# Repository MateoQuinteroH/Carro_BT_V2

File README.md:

# Carro_BT_V2
Carro basado en arduino Nano controlado mediante una aplicación Android

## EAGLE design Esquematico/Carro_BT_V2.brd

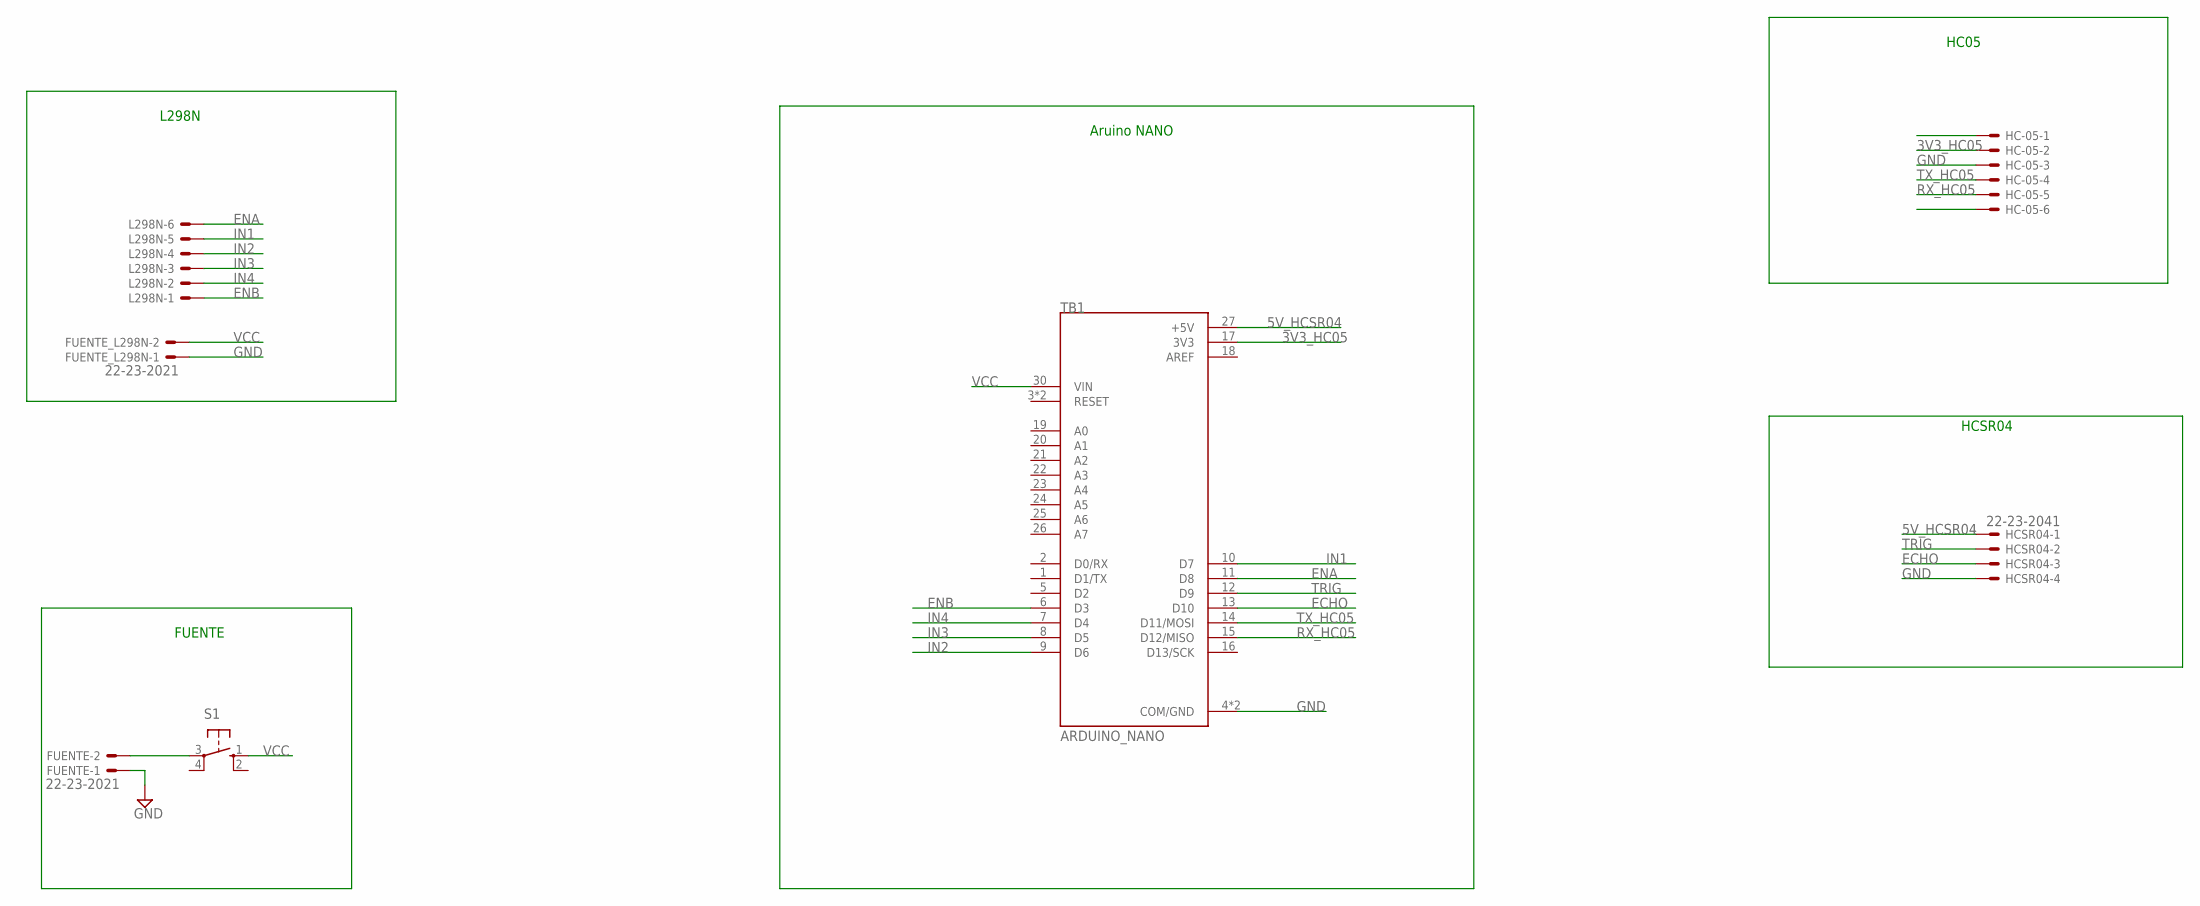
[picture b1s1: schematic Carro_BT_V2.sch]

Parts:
FUENTE: 22-23-2021
FUENTE_L298N: 22-23-2021
HC-05: 22-23-2061
HCSR04: 22-23-2041
L298N: 22-23-2061
S1: 10-XX; B3F-10XX
TB1: ARDUINO_NANO; SHIELD_ARDUINO_NANO

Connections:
3V3_HC05: HC-05.2, TB1.17 (3V3)
5V_HCSR04: HCSR04.1, TB1.27 (+5V)
AREF: TB1.18 (AREF)
ECHO: HCSR04.3, TB1.13 (D10)
ENA: L298N.6, TB1.11 (D8)
ENA1: HC-05.6
ENB: L298N.1, TB1.6 (D3)
ENB1: HC-05.1
GND: FUENTE.1, FUENTE_L298N.1, HC-05.3, HCSR04.4, TB1.4 (COM/GND), TB1.29 (COM/GND)
IN1: L298N.5, TB1.10 (D7)
IN2: L298N.4, TB1.9 (D6)
IN3: L298N.3, TB1.8 (D5)
IN4: L298N.2, TB1.7 (D4)
unnamed: FUENTE.2, S1.3
RX_HC05: HC-05.5, TB1.15 (D12/MISO)
TRIG: HCSR04.2, TB1.12 (D9)
TX_HC05: HC-05.4, TB1.14 (D11/MOSI)
VCC: FUENTE_L298N.2, S1.1 (S), TB1.30 (VIN)

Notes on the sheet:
Aruino NANO
L298N
HC05
HCSR04
FUENTE

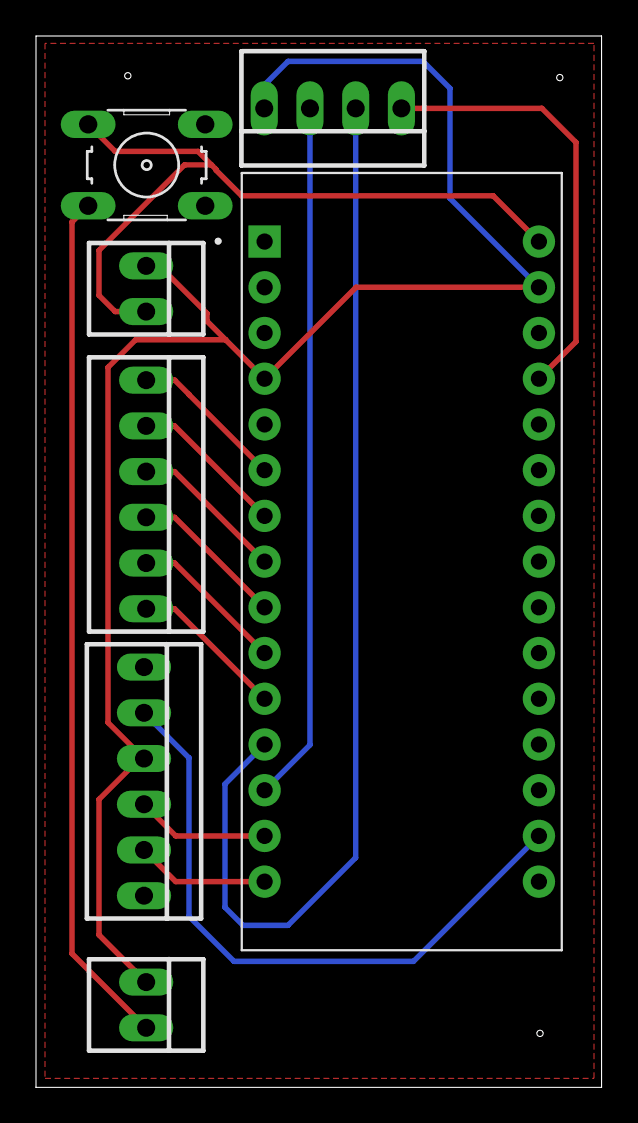
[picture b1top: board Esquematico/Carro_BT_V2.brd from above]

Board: 2 copper layers, 31.4 x 58.4 mm, 7 parts (0 on the bottom side), 15 nets.

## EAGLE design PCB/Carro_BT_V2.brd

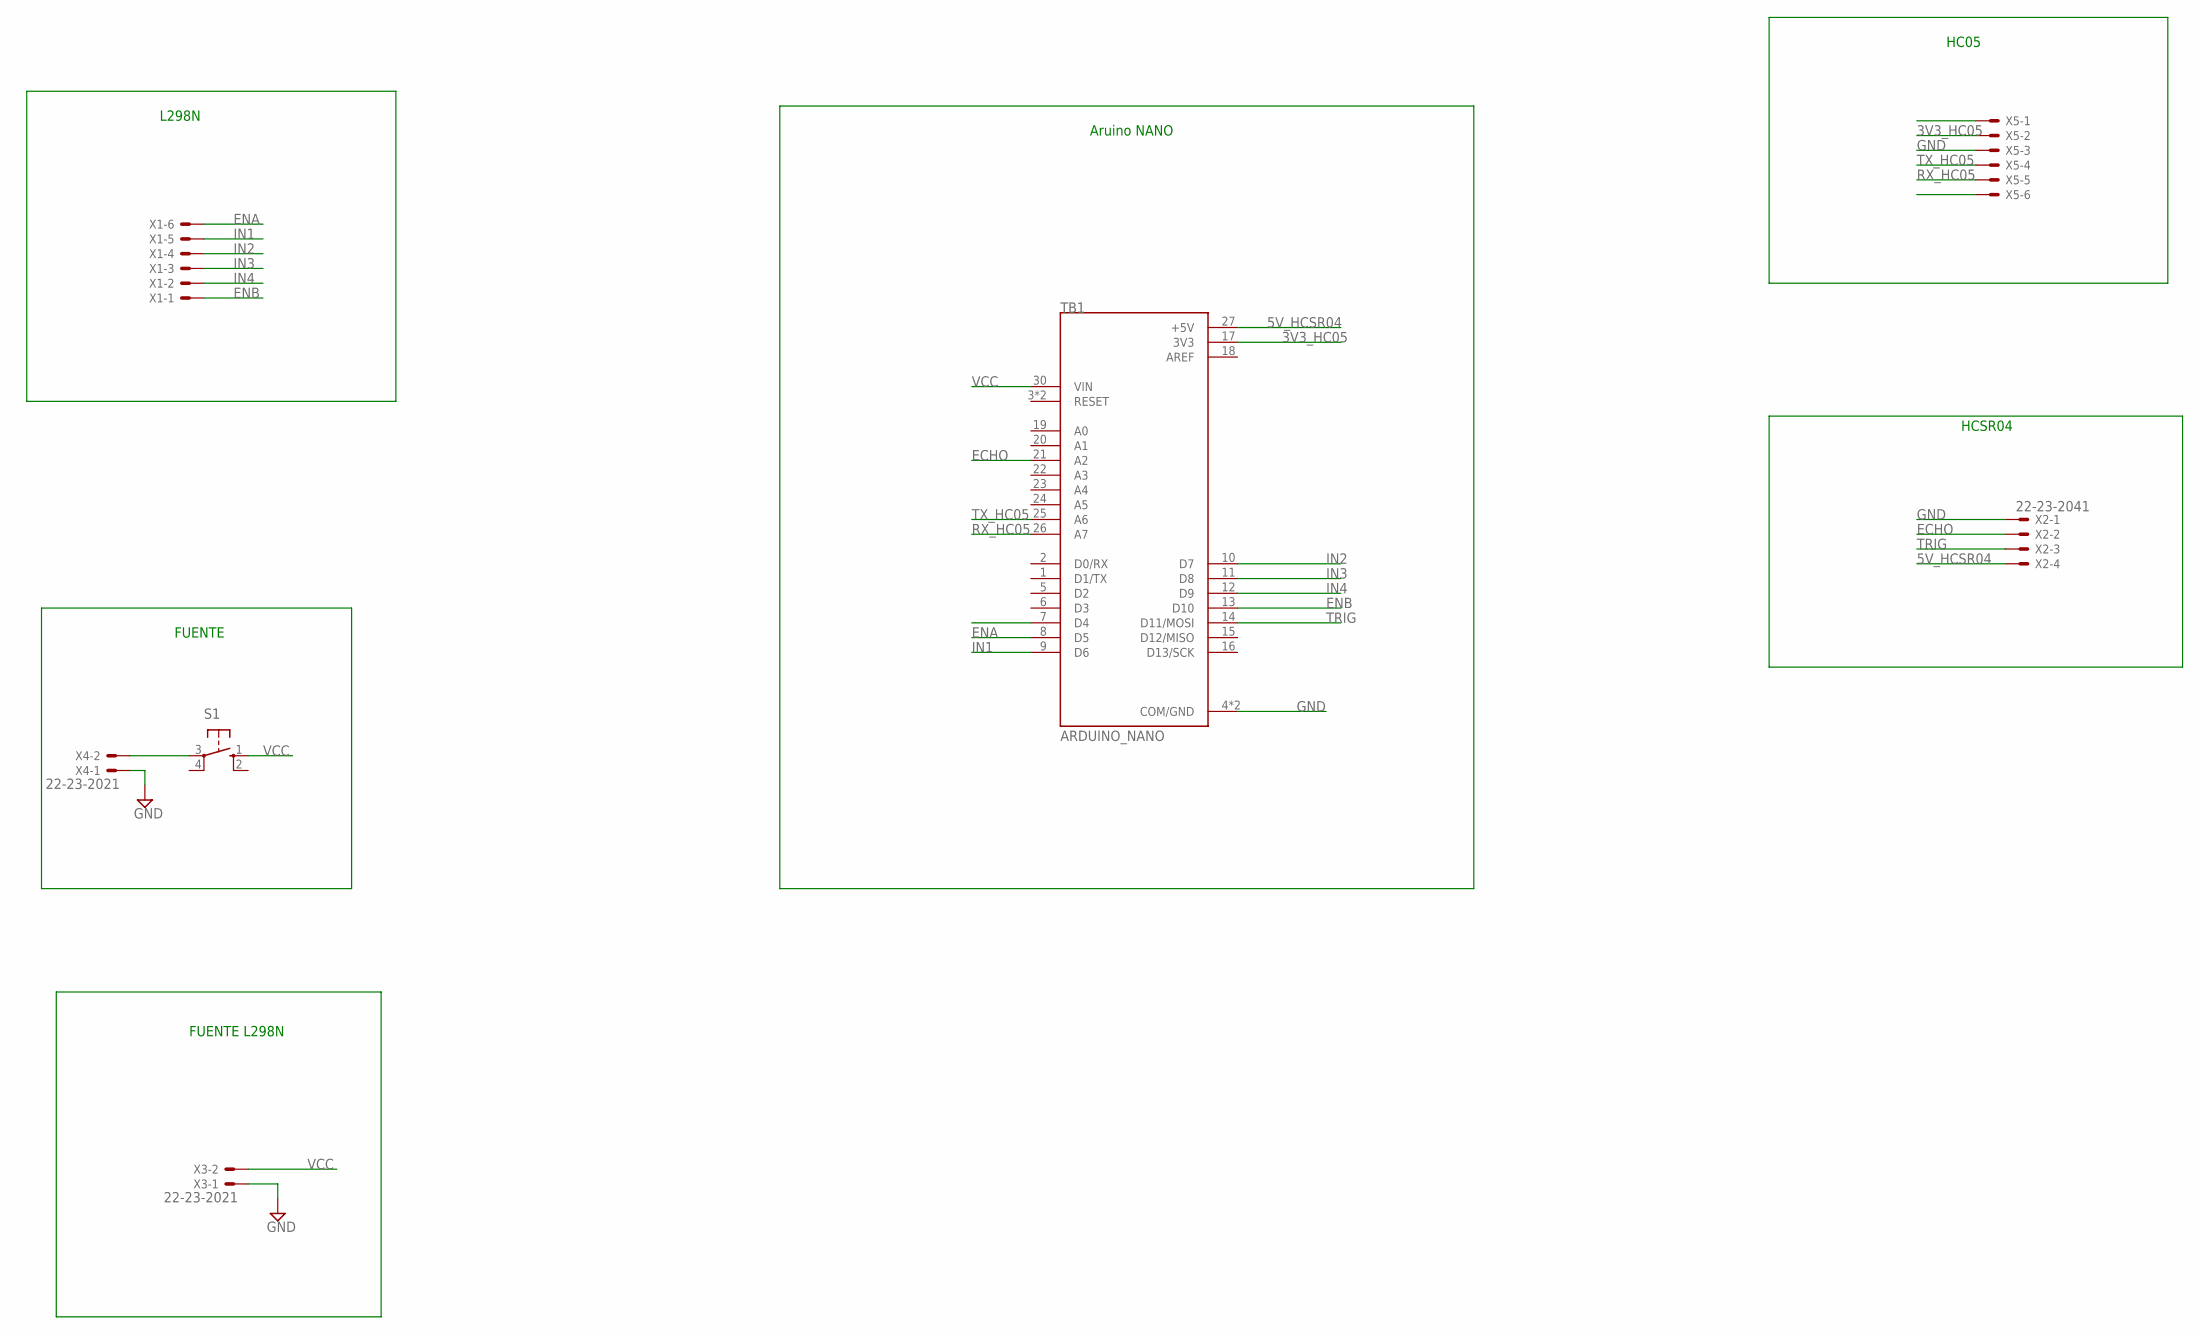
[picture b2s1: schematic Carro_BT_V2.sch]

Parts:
S1: 10-XX; B3F-10XX
TB1: ARDUINO_NANO; SHIELD_ARDUINO_NANO
X1, X5: 22-23-2061
X2: 22-23-2041
X3, X4: 22-23-2021

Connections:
3V3_HC05: TB1.17 (3V3), X5.2
5V_HCSR04: TB1.27 (+5V), X2.4
AREF: TB1.18 (AREF)
ECHO: TB1.21 (A2), X2.2
ENA: TB1.8 (D5), X1.6
ENB: TB1.13 (D10), X1.1
GND: TB1.4 (COM/GND), TB1.29 (COM/GND), X2.1, X3.1, X4.1, X5.3
IN1: TB1.9 (D6), X1.5
IN2: TB1.10 (D7), X1.4
IN3: TB1.11 (D8), X1.3
IN4: TB1.12 (D9), X1.2
unnamed: S1.3, X4.2
RX_HC05: TB1.26 (A7), X5.5
TRIG: TB1.14 (D11/MOSI), X2.3
TX_HC05: TB1.25 (A6), X5.4
VCC: S1.1 (S), TB1.30 (VIN), X3.2

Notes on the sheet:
Aruino NANO
L298N
HC05
HCSR04
FUENTE
FUENTE L298N

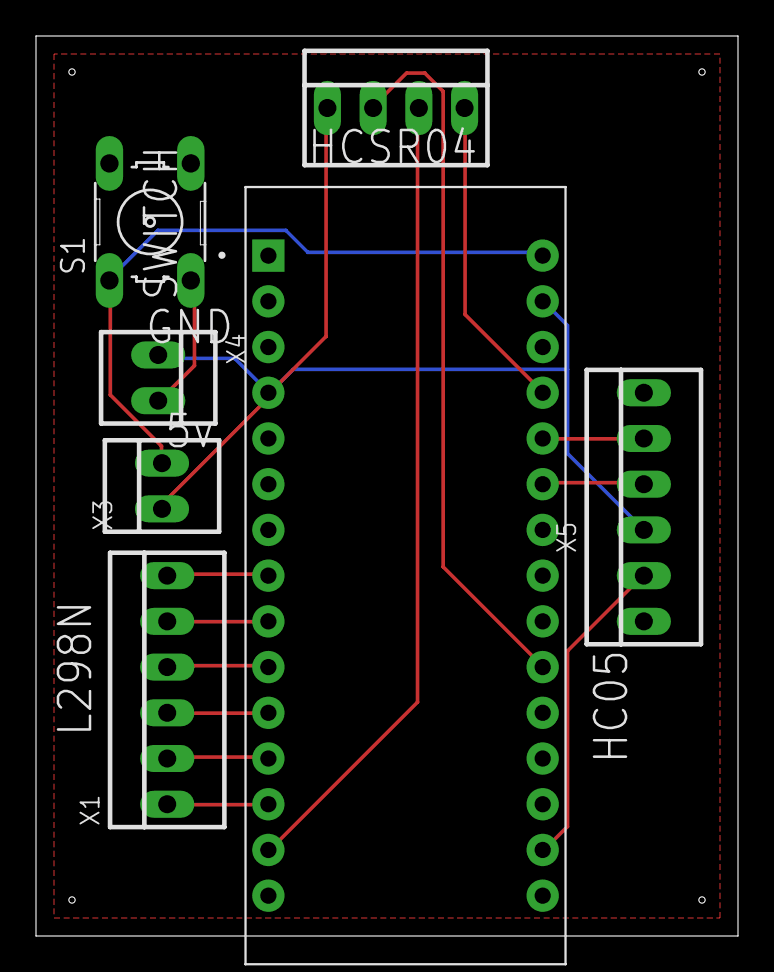
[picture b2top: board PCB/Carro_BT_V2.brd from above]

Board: 2 copper layers, 39.0 x 50.0 mm, 7 parts (0 on the bottom side), 15 nets.

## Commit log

2021-02-23 Archivos del hardware del carro BlueTooth
2021-02-23 Se implementa la comunicación serial entre el arduino UNO y el módem AI Thinker A7
2021-02-23 Se implementa la comunicación serial entre el Arduino UNO y el módulo AI Thinker A7
2021-03-01 Se reduce el tamaño de la PCB para reducir el precio de fabricación.
2021-03-01 PCB con tamaño actualizado para fabricación.
2021-03-01 Archivos de fabricación actualizados
2021-03-01 Libreria EAGLE para Arduino NANO
2021-05-19 Se eliminan las etiquetas del silk screen por problemas en la fabricación, se adicionan mounting holes.
2021-05-19 Se eliminan las etiquetas del silk screen por problemas en la fabricación, se adicionan los mounting holes.
